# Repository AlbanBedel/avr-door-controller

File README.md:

# AVR based wiegand door controller

This project is about building an open source physical access control
system for small communities and groups.

## Electronic

In this directory you will find the hardware design (schematics and PCB) for
a two door controller using an Arduino Nano. Its main features are:

* Can be powered with 12V or 24V.
* Support various setup for the door lock, the relay can be connected to
  12V, 24V or GND as normally open or as normally closed.
* An USB power supply to power additional devices such as an AP for network
  connectivity.
* Use RJ-45 connectors for the doors to allow standardizing the physical
  installation.

This design intentionally doesn't provide network connectivity for two reasons.
First we want to keep the device as cheap and reliable as possible. But most
importantly we want a secure system, implementing secure communication (SSL)
on a small micro-controller is not really possible. So instead of using dubious
Ethernet expansion boards we decided to only provide an USB interface and rely
on external devices running a full OS for access over the network.

### Pin out

	Pin | Function | T-568 A      | T-568 B      | Reader
	------------------------------------------------------
	  1 | Beep     | White Green  | White Orange | Yellow
	  2 | LED      | Green        | Orange       | Blue
	  3 | Status   | White Orange | White Green  |
	  4 | D1       | Blue         | Blue         | White
	  5 | D0       | White Blue   | White Blue   | Green
	  6 | Relay    | Orange       | Green        |
	  7 | 12V      | White Brown  | White Brown  | Red
	  8 | GND      | Brown        | Brown        | Black

## Firmware

In this directory you will find the firmware for the above hardware,
it supports both the Arduino Nano version 2 and version 3. We recommend using
version 3 as they have a much large EEPROM which allow for up to 200 access
records.

The firmware currently support:

* 26 bits wiegand RFID readers
* RFID reader with keypad for PIN
* Access with PIN only, card only or card + PIN
* TOTP and HOTP PIN
* Simple access records management over USB

The following is planned:

* Support external EEPROM for more access records
* 34 bits RFID cards

## Daemon

In this directory you will find a daemon that allow managing one or more
controllers using OpenWrt ubus. As OpenWrt include a JSON-RPC interface to ubus
this daemon allow to manage the controllers over the network using a JSON-RPC
interface.

## Client

In this directory you will find the client software to manage the controllers.
First is a tool (and python API) that allow to manage a controller, either over
USB or over JSON-RPC. This tool is pretty low level but make it easy to setup
a single controller with a couple of users. Then there is database backed tool
that allow to easily manage larger deployments with several controllers and many
users.

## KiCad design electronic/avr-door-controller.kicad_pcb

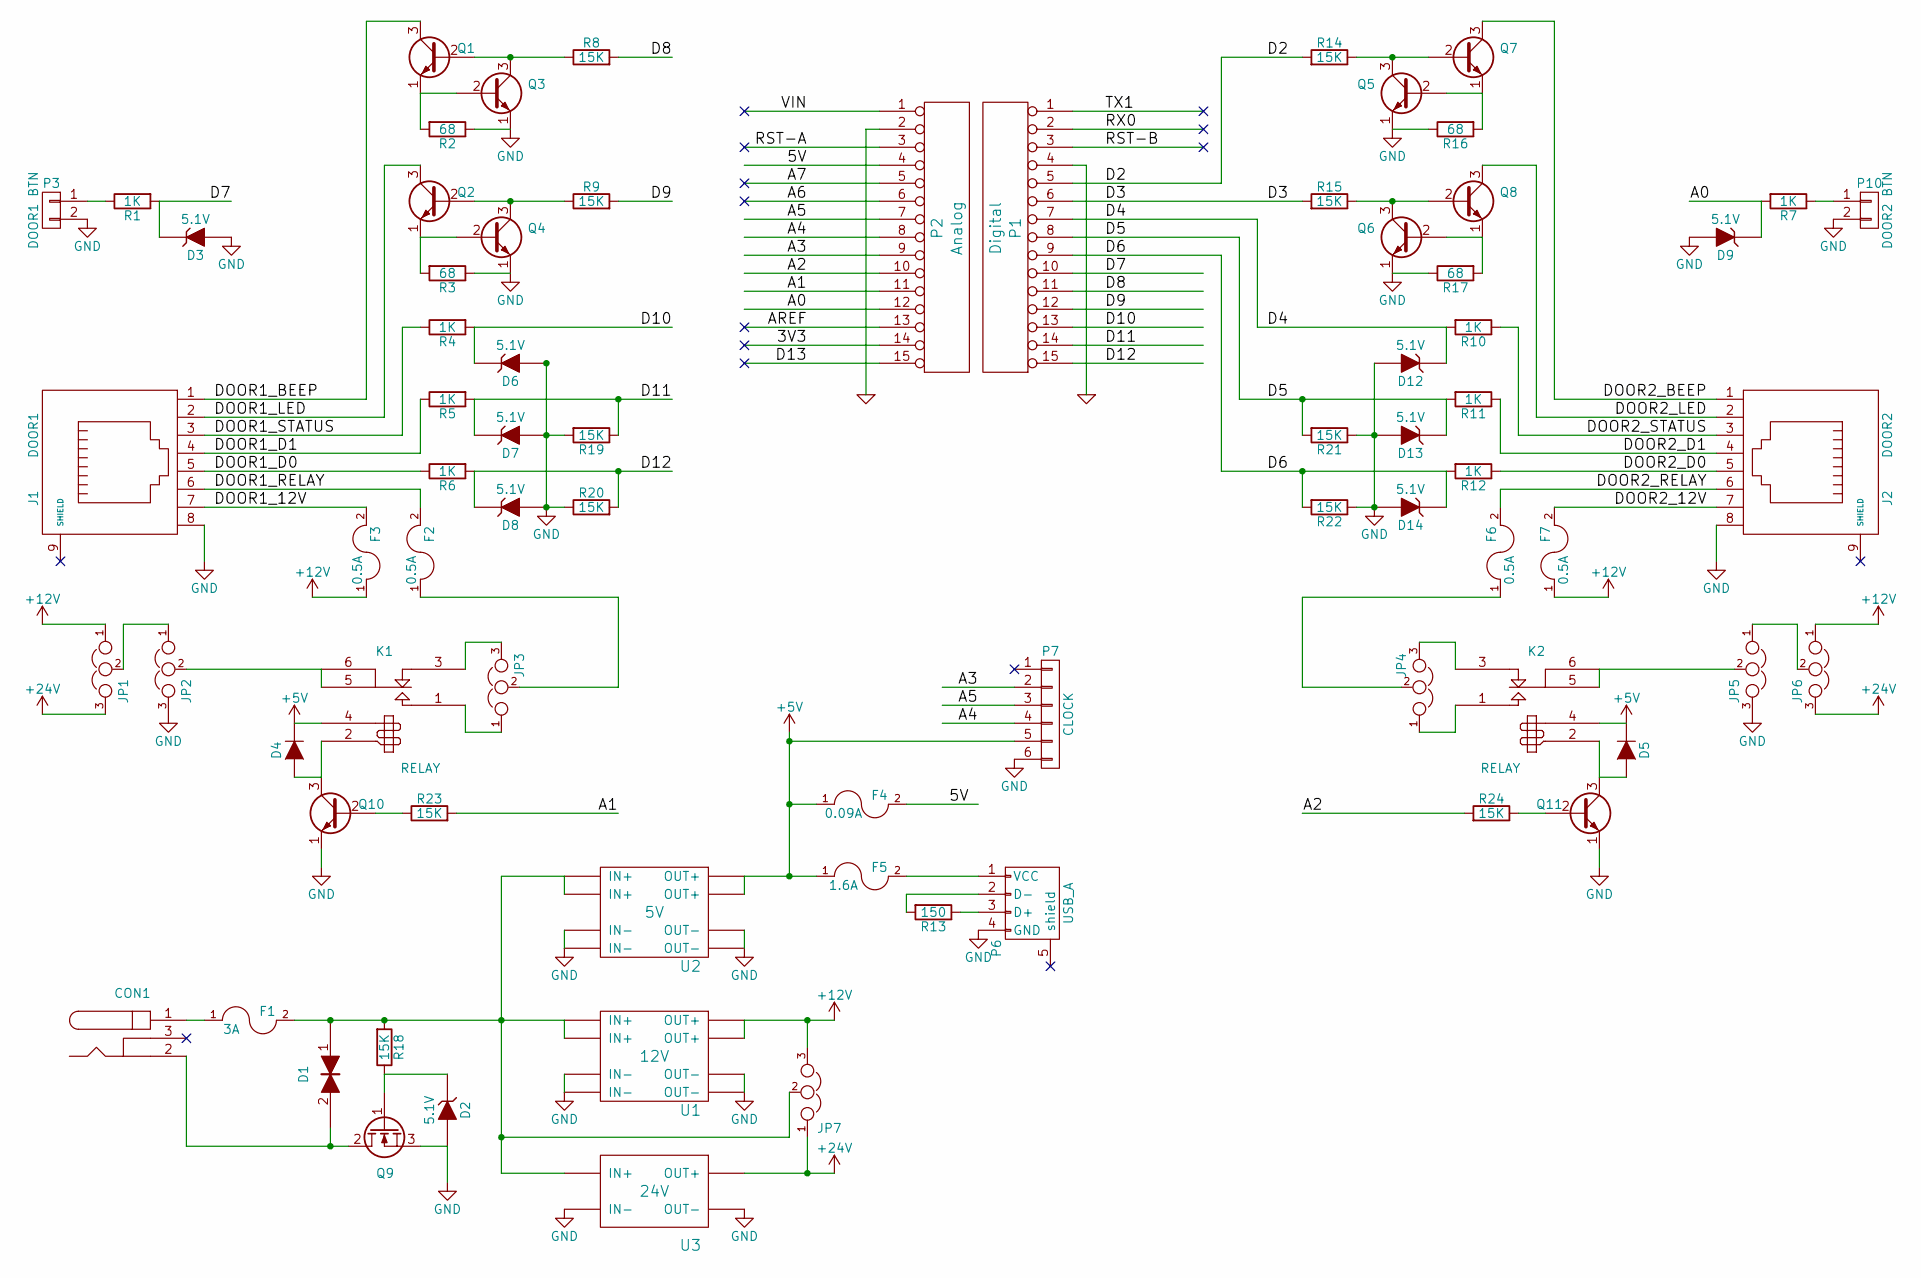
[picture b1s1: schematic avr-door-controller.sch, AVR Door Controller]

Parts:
CON1: 24V; BARREL_JACK; Mouser Part No 490-PJ-002BH
D1: TVS; Diode_DO-41_SOD81_Vertical_AnodeUp; Mouser Part No 750-P4KE30CA-G
D2: 5.1V; Diode_DO-35_SOD27_Horizontal_RM10
D3, D6, D7, D8, D9, D12, D13, D14: 5.1V; Diode_DO-35_SOD27_Horizontal_RM10; Part 1N5231B
D4, D5: 1N4148; Diode_DO-35_SOD27_Horizontal_RM10
F1: 3A; Bourns_PPTC_Style_2; Mouser Part No 652-MFR300
F2: 0.5A; Bourns_PPTC_Style_1; Mouser Part No 530-0ZRC0050FF1E
F3, F6, F7: 0.5A; Bourns_PPTC_Style_1
F4: 0.09A; Bourns_PPTC_Style_1; Mouser Part No 530-0ZRC0015FF1E
F5: 1.6A; Bourns_PPTC_Style_1; Mouser Part No 650-RUEF160-2
J1: DOOR1; RJ45_8; Mouser Part No 649-54602-908LF
J2: DOOR2; RJ45_8
JP1: 12V|24V; PINHEAD1-3; Mouser Part No 538-22-28-4030
JP2, JP5: VCC|GND; PINHEAD1-3
JP3, JP4: NC | NO; PINHEAD1-3
JP6, JP7: 12V|24V; PINHEAD1-3
K1, K2: RELAY; JRC-21F
P1: Digital; Socket_Strip_Arduino_1x15; Mouser Part No 992-15FX1-254MM
P2: Analog; Socket_Strip_Arduino_1x15; Mouser Part No 992-15FX1-254MM
P3: DOOR1 BTN; bornier2; Mouser Part No 504-EM367502
P6: USB_A; Mouser Part No 706-33UBAR-04SW11
P7: CLOCK; PINHEAD1-6; Mouser Part No 855-M20-9990646
P10: DOOR2 BTN; bornier2
Q1, Q3, Q5, Q7: Q_NPN_EBC; TO-92_Inline_Narrow_Oval
Q2, Q10, Q11: Q_NPN_EBC; TO-92_Inline_Narrow_Oval; Part 2N3904; Mouser Part No 833-2N3904-AP
Q4, Q6, Q8: Q_NPN_EBC; TO-92_Inline_Narrow_Oval; Part 2N3904
Q9: Q_NMOS_GDS; TO-251AA; Mouser Part No 942-IRFU7546PBF
R1, R5, R6, R7, R10, R11, R12: 1K; Resistor_Horizontal_RM10mm
R2: 68; Resistor_Horizontal_RM10mm; Mouser Part No 71-CCF0768R0GKE36
R3, R16, R17: 68; Resistor_Horizontal_RM10mm
R4: 1K; Resistor_Horizontal_RM10mm; Mouser Part No 594-SFR25H0001001JA5
R8, R23, R24: 15K; Resistor_Horizontal_RM10mm; Mouser Part No 603-MFR-25FBF52-15K
R9, R14, R15, R18, R19, R20, R21, R22: 15K; Resistor_Horizontal_RM10mm
R13: 150; Resistor_Horizontal_RM10mm; Mouser Part No 603-MFR-25FBF52-150R
U1: 12V; XM1584
U2: 5V; XM1584
U3: 24V; MT3608

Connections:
+5V: D4.1 (K), D5.1 (K), F4.1, F5.1, K1.4, K2.4, P7.5, U2.7 (OUT+), U2.8 (OUT+)
+12V: F3.1, F7.1, JP1.1, JP6.1, JP7.3, U1.7 (OUT+), U1.8 (OUT+)
+24V: JP1.3, JP6.3, JP7.1, U3.4 (OUT+)
/3V3: P2.14
/5V: F4.2, P2.4
/A0: D9.1 (K), P2.12, R7.2
/A1: P2.11, R23.2
/A2: P2.10, R24.2
/A3: P2.9, P7.2
/A4: P2.8, P7.4
/A5: P2.7, P7.3
/A6: P2.6
/A7: P2.5
/AREF: P2.13
/D2: P1.5, R14.2
/D3: P1.6, R15.2
/D4: D12.1 (K), P1.7, R10.2
/D5: D13.1 (K), P1.8, R11.2, R21.2
/D6: D14.1 (K), P1.9, R12.2, R22.2
/D7: D3.1 (K), P1.10, R1.2
/D8: P1.11, R8.2
/D9: P1.12, R9.2
/D10: D6.1 (K), P1.13, R4.2
/D11: D7.1 (K), P1.14, R5.2, R19.1
/D12: D8.1 (K), P1.15 (p15), R6.2, R20.2
/D13: P2.15 (p15)
/DOOR1_12V: F3.2, J1.7
/DOOR1_BEEP: J1.1, Q1.3 (C)
/DOOR1_D0: J1.5, R6.1
/DOOR1_D1: J1.4, R5.1
/DOOR1_LED: J1.2, Q2.3 (C)
/DOOR1_RELAY: F2.2, J1.6
/DOOR1_STATUS: J1.3, R4.1
/DOOR2_12V: F7.2, J2.7
/DOOR2_BEEP: J2.1, Q7.3 (C)
/DOOR2_D0: J2.5, R12.1
/DOOR2_D1: J2.4, R11.1
/DOOR2_LED: J2.2, Q8.3 (C)
/DOOR2_RELAY: F6.2, J2.6
/DOOR2_STATUS: J2.3, R10.1
/RST-A: P2.3
/RST-B: P1.3
/RX0: P1.2
/TX1: P1.1
/VIN: P2.1
GND: D2.2 (A), D3.2 (A), D6.2 (A), D7.2 (A), D8.2 (A), D9.2 (A), D12.2 (A), D13.2 (A), D14.2 (A), J1.8, J2.8, JP2.3, JP5.3, P1.4, P2.2, P3.2, P6.4 (GND), P7.6, P10.2, Q3.1 (E), Q4.1 (E), Q5.1 (E), Q6.1 (E), Q9.3 (S), Q10.1 (E), Q11.1 (E), R2.1, R3.1, R16.1, R17.1, R19.2, R20.1, R21.1, R22.1, U1.3 (IN-), U1.4 (IN-), U1.5 (OUT-), U1.6 (OUT-), U2.3 (IN-), U2.4 (IN-), U2.5 (OUT-), U2.6 (OUT-), U3.1 (IN-), U3.3 (OUT-)
unnamed: CON1.1, F1.1
unnamed: CON1.2, D1.2, Q9.2 (D)
unnamed: D1.1, F1.2, JP7.2, R18.2, U1.1 (IN+), U1.2 (IN+), U2.1 (IN+), U2.2 (IN+), U3.2 (IN+)
unnamed: D2.1 (K), Q9.1 (G), R18.1
unnamed: D4.2 (A), K1.2, Q10.3 (C)
unnamed: D5.2 (A), K2.2, Q11.3 (C)
unnamed: F2.1, JP3.2
unnamed: F5.2, P6.1 (VCC)
unnamed: F6.1, JP4.2
unnamed: JP1.2, JP2.1
unnamed: JP2.2, K1.5 (C1), K1.6
unnamed: JP3.1, K1.1 (T1)
unnamed: JP3.3, K1.3 (R1)
unnamed: JP4.1, K2.1 (T1)
unnamed: JP4.3, K2.3 (R1)
unnamed: JP5.1, JP6.2
unnamed: JP5.2, K2.5 (C1), K2.6
unnamed: P3.1, R1.1
unnamed: P6.2 (D-), R13.2
unnamed: P6.3 (D+), R13.1
unnamed: P10.1, R7.1
unnamed: Q1.1 (E), Q3.2 (B), R2.2
unnamed: Q1.2 (B), Q3.3 (C), R8.1
unnamed: Q2.1 (E), Q4.2 (B), R3.2
unnamed: Q2.2 (B), Q4.3 (C), R9.1
unnamed: Q5.2 (B), Q7.1 (E), R16.2
unnamed: Q5.3 (C), Q7.2 (B), R14.1
unnamed: Q6.2 (B), Q8.1 (E), R17.2
unnamed: Q6.3 (C), Q8.2 (B), R15.1
unnamed: Q10.2 (B), R23.1
unnamed: Q11.2 (B), R24.1

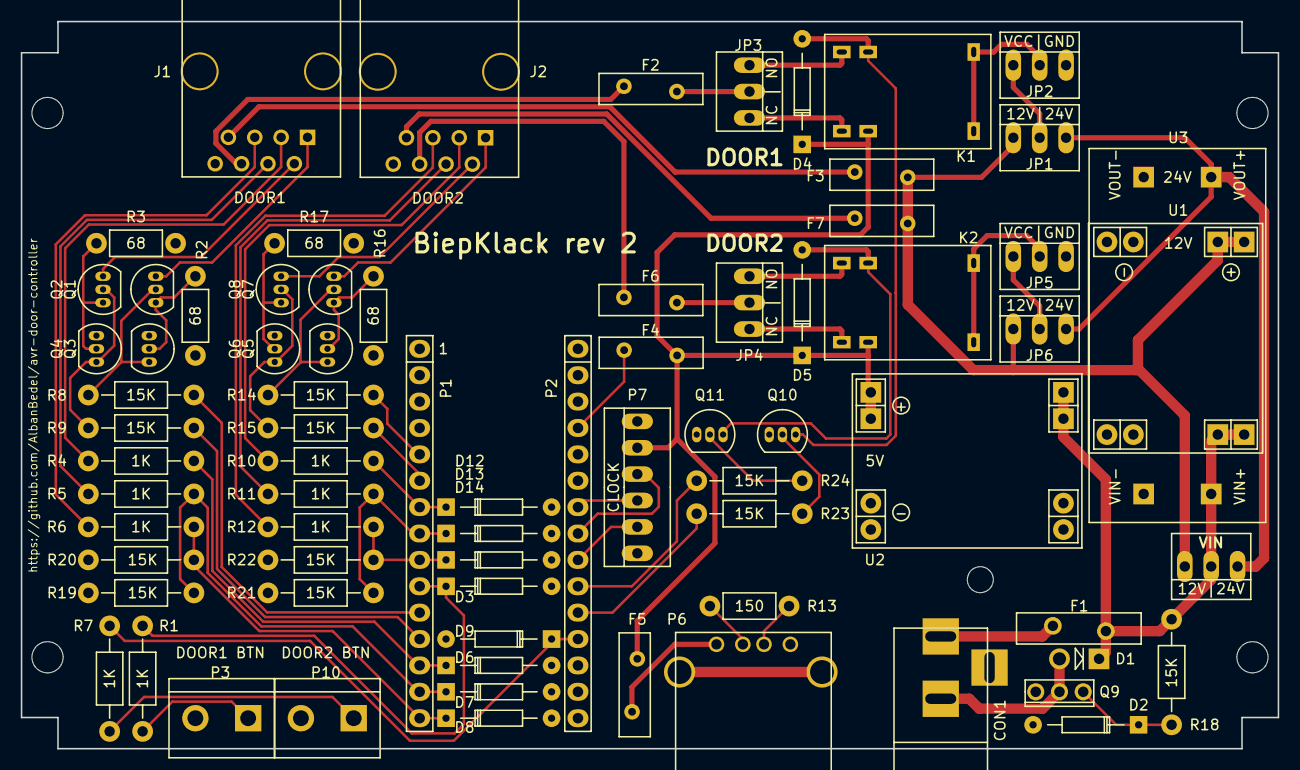
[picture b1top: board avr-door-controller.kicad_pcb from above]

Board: 2 copper layers, 121.0 x 70.0 mm, 75 parts (0 on the bottom side), 67 nets.

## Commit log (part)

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2017-04-06 Initial version
2017-04-06 trigger: Skip empty steps instead of using a 0 timeout
    This simplify the process a bit and avoid useless timeouts.
2017-05-02 build: Fix the CFLAGS to fix EEPROM generation with new gcc versions
    In current gcc version when LTO is enabled we need to add
    -ffat-lto-objects to the CFLAGS for the normal EEPROM section to be
    present in the object files.
2017-05-02 door ctrl: Rework the event handling to prevent potential races
    Currently the door controller state is changed from timer handlers.
    This is a problem because they run from interrupt handlers so the
    state might change while we handle an event.
    To prevent this we now generate events from the timeout handler and
    then handle the state change from the event handler. To spare some
    memory we use the same handler as for the wiegand events, so the events
2017-05-02 wiegand reader: Make WIEGAND_READER_ERROR an unsigned value
    The negative value for WIEGAND_READER_ERROR produce a warning when
    used in a switch, so replace it with 0xFF.
2017-05-02 eeprom: Move the records types to a dedicated header
    These data type will be needed for the control protocol, move them to
    a dedicated header to allow reusing them without the rest of the
    eeprom API.
2017-08-09 ctrl cmd: Move the method array to flash storage
    No need to use the RAM for such const data, move it to the flash.
2017-08-12 ctrl-cmd: Add a command to clear all the access records at once
2017-09-06 electronic: Add a .gitignore
    Keep all the generated and backup files out of git's way.
2017-09-15 firmware: gpio: Add a macro to change a GPIO polarity
2017-09-15 electronic: pcb: Platte the mounting holes of the USB connector
    For some reason I removed the platting on the mounting holes of the
    USB connector. This prevent properly soldering the connector, so set
    the platting back.
2017-09-15 firmware: Turn on the LED and go to sleep if the init fails
    There is not much we can do in this case but that should gives the
    user a hint that something is wrong with the controller.
2017-09-15 firmware: external irq: Add an IRQ lookup from GPIO
    Add a function that allow looking up the IRQ mapped to a GPIO.
2017-09-15 firmware: trigger: Allow restarting an already running sequence
    Sometimes we want to restart an already running sequence, so fix
    stopping a running one, and don't forbid restarting.
2017-09-15 completion: Sleep when waiting for a completion
    Completion always happen from an ISR, so we might as well sleep
    instead running a busy loop.
2017-09-15 firmware: door ctrl: Add the open button and status input
    Rework the door opening handling to support an external open button.
    While at it we also add the status input as button although it isn't
    handled yet.
2017-09-15 daemon: Rework the access record get/set methods
    * Use an integer type for every card field
    * Change the get result to use a 'pin' and/or 'card' field
    instead of the 'key' field.
    * Also allow passing a 'pin' or 'card' field to get a fully decoded
    record for pin+card records.
    * Make the 'card', 'pin' and 'doors' fields of the set_access_record
2017-09-16 firmware: Add a board define for the life indicator GPIO
2017-09-27 electronic: schematics: Add the MT3608 step up module
2017-09-27 electronic: Add the footprint for the JRC-21F relay
2017-10-22 build: Add basic support for Travis CI
    Check that the firmware builds correctly for all supported boards
2017-10-31 daemon: Add the set_door_config command
    Implement the missing set_door_config command to allow setting the
    open time of a door.
2017-11-25 electronic: footprint: Fix the pads of the MT3608 to match the XM1584
    Better use the same pads on both modules, we will solder both in the
    same way.
2018-01-21 client: Add a command line client to manage the database
    This client allow to manage larger deployment with several doors and
    many users. It allow easily adding creating and managing users, groups
    and the door access list. Furthermore it allow to synchronize the ACL
    stored in the database with the hardware controllers.
2018-02-03 client: AVRDoorCtrl: Add some error message to validation exceptions
    Tell the user what was wrong when we abort because of bad arguments.
2018-02-21 client: AVRDoorsDB: Remove useless parameter checks in Door.add_access()
    Door.add_access() first call Door.get_access() which already check
    that the parameters are valid, so there is no need to duplicate these
    checks in Door.add_access().
2018-02-21 client: AVRDoorsDB: The Controller.uobject column doesn't exists
    The uobject column existed in early versions of the database, but it
    has been removed so it shouldn't be in the Controller class anymore.
2018-02-21 client: admin: Rework the `door add` and `door update` commands
    Rework the `door add` and `door update` commands now that the
    controller is optional. We make the controller and port optional for
    the `add` command and extend the `update` command to allow deleting
    these fields.
2018-03-09 client: DB: Fix the where clause generation
    The generated where clause didn't include the provided condition as
    expected.
2018-03-09 client: admin: Show all access that the user have in `user show`
    Add a new field to AVRDoorsDB.User that use the AllAccess view
    to get a full list of the user access, including those from the
    groups. Then rework `user show` to display this access list instead of
    just the personal door access.
2018-11-22 firmware: Set the arduino nano v3 as default build target
    As we don't have any v2 hardware around anymore better use v3 as the
    default target.
2018-11-22 ctrl-cmd: Add a command to get the unused access records
    Add a command that allow to get all the unused records, and can
    optionaly clear the used flag. This command can be run at regular
    interval to see if cards are beeing used or not.
2018-11-23 firmware: ctrl-cmd: Add a ping command to check on the device
    Add a ping command to allow the daemon to quickly check if the device
    is alive.
2018-11-26 client: DB: Add a boolean datatype
    Add a boolean type that return python bool() from the database and has
    sensible parsing. It accept only Yes/No, y/n, True/False, t/f or a
    numerical value.
2018-11-26 client: db: Add fields and view to track unused ACL in controllers
    Add a LastUsedCheck field to the ControllerSetACL table to allow to
    track ACL that are beeing used, a LastUseCheck field to the Controller
    table to track when this check was last done on the controller, and a
    view to easily list the ACL along with how long they haven't been used.
2019-10-21 client: db: Simplfiy the Controller.get_door method
    Use our DB API to directly request the matching Door object instead of
    using the low level API, that make the code a bit simpler.
2019-10-21 ctrl-cmd: Add a command to get the access records that have been used
    Add a command that allow getting all the used records, and can
    optionaly clear the used flag. This command can be run at regular
    interval to check if cards are beeing used or not.
2019-10-21 daemon: Add support for iterative commands
    Currently ubus methods map one to one with a firmware command,
    however the new command to get used access records must be sent
    repetitively until we have all relevent records.
    To allow this the result parsing function can now return -EAGAIN
    to indicate that it is not finished. The main loop will then call a
    new callback, `write_continue_query` that create the new command from
2020-10-01 client: ACRDoorCtrl: Add the get_used_access method
    Add the get_used_access method for local uart and remote ubus.
2020-10-01 daemon: Use a wrapper to start sending data
    Add a wrapper around the uloop fd to make the code more readable.
2020-10-01 firmware: Increase the firmware version to 0.2
2025-08-11 client: DB: ObjectList: Add del and append
    Allow to use the normal del and append to manipulate the list.
2025-08-11 utils: Add the container_of macro from linux
    This macro is useful to avoid having to pass a context pointer around.
    It will be needed by the upcoming API changes.
2025-08-11 client: DB: Improve error handling when loading objects
    Only clear the object if an error happen after we started modifying
    it, this keep the object as is if the error happen earlier.
2025-08-11 client: Mark users without cards in group and access lists
    When showing user lists it is useful to directly see users that have
    no card, as they can't do anything anyways.
2025-08-11 firmware: Let `make clean` also take care of the sub directories
    The temporaty files created in mcu/ and boards/ must also be removed
    by `make clean`.
2025-08-11 client: admin: Allow configuring the DB from the environment
    To ease usage in containers get the defaults for the DB connection
    parameters from the MYSQL_* environment variables.
2025-08-11 client: Raise a TimeoutError when no data can be read from UART
    Use the correct exception when we stop receiving data from the UART.
2025-08-11 client: Convert common error codes to string
    Add an strerror() implementation so we can put a description of the
    error in the exception instead of just the errno code. We can't
    fallback on the libc here as the errno values are platform specific.
2025-08-11 client: DB: Add server side OTP support
    Implementing OTP support in the firmware is major change that is still
    not finished. As a workaround we instead implement this feature in the
    database. For the rest of the software stack the OTP PIN are just
    normal PIN that are generated by the database. A big down side of this
    is the strain on the controllers EEPROM, so timeout shorter than 8 hours
    shouldn't be used. Also the controllers will get out of sync if they
2025-08-11 firmware: Send the device descriptor with the `started` event
    Send the device descriptor with the `started` event so client software
    have the firmware version from the get go.
2025-08-11 client: DB: Finish fixing the schema for MariaDB 10.6
    Now the `offset` is reserved keyword it can't be used anywhere. Rename
    the variable in the `HOTP` function and quote the column name use.
2025-08-11 client: DB: Properly handle the removal of lists elements
    If a list element is deleted using its `delete` method instead of using
    `del` on its containing array the array would get out of sync.
    Allow database objects to have a custom delete handler so the list can
    put its own handler when creating its items. Through this handler the
    list items are always deleted by removing them from their list.
2025-08-11 client: Add support for the new access records
    The new access records add support for HOTP and TOTP. All access
    record related methods in the AVRDoorCtrl class can now return either
    the old or new format. When possible the native transport commands for
    the requested format are used. If they are not supported a fallback is
    used with the other command and the result is converted.
2025-08-11 client: Add support for showing the access and door status events
    Add the parsing code to show the events returned when an access is
    attempted of when the door status changes.
2025-08-11 firmware: Add a controller config to store the OTP root key
    A root key is needed to derive the OTP secrets, it is stored in EEPROM
    before the door configuration. This loose some access record space so
    the opportunity is used to also remove unused fields in the door config.
    Two control commands are added to allow getting and setting the
    controller config. Unless build with debug the getter always return an
    empty key. Similarly the setter only overwrite the key if a new one is
